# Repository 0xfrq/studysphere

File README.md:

# StudySphere: Smart Study Room (UTS/UAS IoT)

Node IoT berbasis ESP32 untuk ruang belajar pintar. Node membaca suhu, kelembapan, cahaya, kualitas udara dan kehadiran orang, menyalakan lampu belajar secara otomatis, menampilkan status di LCD, dan berkomunikasi dengan aplikasi desktop lewat **MQTT**. Aplikasi desktop (Tauri, Windows dan Linux) ada di `desktop/` dan sekaligus menjadi broker MQTT di laptop, jadi sistemnya berdiri sendiri tanpa internet. LLM lokal dikerjakan terpisah dan memakai kontrak MQTT di bawah.

## Komponen dan wiring

| Komponen | Pin modul | ESP32 | Daya |
|---|---|---|---|
| DHT11 (suhu & kelembapan) | DATA | GPIO4 | 3V3 |
| Modul LDR (LM393) | AO | GPIO34 | 5V |
| MQ-135 (kualitas udara / CO2) | AO | GPIO35 | 5V |
| HC-SR501 PIR (kehadiran) | OUT | GPIO27 | 5V |
| LCD 16x2 I2C (alamat 0x27) | SDA, SCL | GPIO21, GPIO22 | 5V |
| LED lampu belajar + resistor 220 Ω | anoda lewat resistor | GPIO13 | |

Semua GND disambung ke GND ESP32. Rangkaiannya ada di `diagram.json` dan bisa dibuka di WireLab atau Wokwi.

Untuk perangkat asli, pakai PCB di `hardware/` (lihat [PCB dan daftar komponen](#pcb-dan-daftar-komponen)). Bedanya dengan rangkaian simulator:

- Modul LDR diberi daya 3V3, jadi output AO-nya tidak pernah melewati batas ADC ESP32 (sekitar 3,1 V).
- AO MQ-135 bisa sampai 5 V, jadi masuk ke GPIO35 lewat pembagi 10 kΩ/15 kΩ dan maksimal 3,0 V.
- LCD tetap 5 V, tapi SDA dan SCL lewat level shifter BSS138, jadi pin ESP32 hanya melihat 3,3 V.
- Aktifkan `#define REAL_BOARD` di `firmware/config.h`. Firmware lalu membaca tegangan asli dengan `analogReadMilliVolts()` dan menghitung LDR 3,3 V serta pembagi MQ-135. Tanpa itu, firmware memakai skala simulator: ADC ESP32 membaca 0 sampai 5 V sebagai 0 sampai 4095.
- Konstanta kalibrasi LDR dan MQ-135 (`LDR_RL10`, `MQ_RZERO` dan seterusnya) ada di atas `firmware.ino`. `MQ_RZERO` sebaiknya dikalibrasi di udara bersih.
- Modul DHT11 tiga pin sudah punya resistor pull-up. PCB juga punya pull-up 10 kΩ (R1), jadi DHT11 empat pin tanpa modul juga bisa disambung lewat kabel jumper.

## PCB dan daftar komponen

Proyek KiCad 10 ada di `hardware/`; buka `hardware/studysphere.kicad_pro`. ERC dan DRC bersih, dan PCB sama dengan skematik (schematic parity).

| File | Isi |
|---|---|
| `hardware/fab/skematik.pdf` | Skematik untuk laporan atau dicetak |
| `hardware/fab/render-top.png`, `render-bottom.png` | Tampilan 3D PCB |
| `hardware/fab/pcb-top.pdf`, `pcb-bottom.pdf` | Jalur tembaga dan silkscreen tiap sisi |
| `hardware/fab/gerber-jlcpcb.zip` | Gerber dan file drill, siap diunggah ke JLCPCB atau PCBWay |
| `hardware/fab/bom.csv` | Daftar komponen dari KiCad |

PCB 2 layer, 102 × 62 mm, tebal 1,6 mm, dengan lubang M3 di keempat sudut. ESP32-DevKitC V4 ditancap ke dua female header 1x19 (jarak baris 25,4 mm): antena di tepi atas, USB di tepi bawah. Di bawah antena tidak ada tembaga. Kedua sisi PCB diisi GND. Jalur daya 0,6 mm, jalur sinyal 0,3 mm.

**Komponen yang disolder ke PCB**

| Jumlah | Komponen | Ref | Fungsi |
|---|---|---|---|
| 6 | Resistor 10 kΩ 1/4 W | R1, R2, R4, R5, R6, R7 | Pull-up DHT11, pembagi MQ-135 (atas), pull-up I2C |
| 1 | Resistor 15 kΩ 1/4 W | R3 | Pembagi MQ-135 (bawah) |
| 1 | Resistor 220 Ω 1/4 W | R8 | Arus LED, sekitar 6 mA |
| 2 | Kapasitor keramik 100 nF (kode 104) | C2, C3 | Filter ADC LDR dan MQ-135 |
| 1 | Kapasitor elektrolit 100 µF 16 V | C1 | Menahan lonjakan arus heater MQ-135 |
| 2 | MOSFET N-channel BSS138 (SOT-23) | Q1, Q2 | Level shifter I2C 3,3 V ke 5 V |
| 1 | LED kuning 5 mm | D1 | Lampu belajar |
| 4 | Pin header male 1x3 | J1 sampai J4 | DHT11, PIR, LDR, MQ-135 |
| 1 | Pin header male 1x4 | J5 | LCD I2C (urutan GND, VCC, SDA, SCL seperti backpack-nya) |
| 2 | Female header 1x19 | U1 | Soket ESP32-DevKitC V4 |
| 4 | Baut M3 dan spacer | H1 sampai H4 | Kaki PCB |

**Modul dan lainnya:** ESP32-DevKitC V4 (38 pin), modul DHT11, HC-SR501, modul LDR, modul MQ-135, LCD 16x2 dengan backpack I2C PCF8574, 16 kabel jumper female-female, dan kabel micro-USB data.

- R2 dan R3 sebaiknya metal film 1% supaya faktor pembagi MQ-135 tepat. Resistor lain boleh 5%.
- Sebelum memesan, ukur jarak dua baris pin DevKit kamu: harus 25,4 mm dengan urutan pin seperti DevKitC V4 resmi (3V3, EN, VP sampai 5V di satu sisi). Beberapa klon 38 pin punya jarak atau urutan lain.
- Urutan solder: Q1 dan Q2 dulu (SMD paling kecil), lalu resistor, kapasitor, LED, pin header, dan female header terakhir. Kaki + C1 masuk ke pad bertanda +, kaki pendek LED (katoda) ke pad kotak.
- Di JLCPCB, unggah `gerber-jlcpcb.zip`, pilih 2 layer dan tebal 1,6 mm, pengaturan lain biarkan default. Kalau PCB diubah di KiCad, buat ulang Gerber lewat **File > Fabrication Outputs**.
- Arus total sekitar 450 mA (ESP32 dengan WiFi, heater MQ-135 sekitar 150 mA, backlight LCD), jadi pakai port USB dan kabel yang bagus.

## Cara kerja

- Sensor dibaca setiap 2 detik. Telemetry dikirim setiap 5 detik, dan langsung saat kehadiran atau lampu berubah.
- **Kehadiran:** PIR mendeteksi gerakan. Sesi belajar dimulai saat ada gerakan dan berakhir setelah 60 detik tanpa gerakan (`IDLE_MS`).
- **Lampu belajar:** mode `auto` menyalakan lampu saat ada orang dan cahaya di bawah 150 lux (`DARK_LUX`). Mode `on` atau `off` bisa dipilih dari aplikasi desktop.
- **Kualitas udara:** CO2 di atas 1000 ppm (`CO2_STALE`) dianggap `stale`, artinya ruangan perlu dibuka atau diberi ventilasi.
- **LCD:** baris 1 berisi suhu, kelembapan dan cahaya (`25.0C 50%  500lx`). Baris 2 berisi CO2 dan status koneksi (`CO2  400ppm MQTT`; `WIFI` berarti WiFi tersambung tapi broker belum, `----` berarti offline). Pesan dari aplikasi desktop tampil di LCD selama 30 detik, maksimal 32 karakter untuk dua baris.

## MQTT

Broker: aplikasi desktop di laptop, port 1883 (lihat [Aplikasi desktop](#aplikasi-desktop)). Semua topik diawali `studysphere/room-01/` (`TOPIC_ROOT` dan `DEVICE_ID` di `firmware/config.h`).

| Topik | Arah | Isi |
|---|---|---|
| `studysphere/room-01/telemetry` | node ke desktop | Semua data, setiap 5 detik dan saat ada perubahan |
| `studysphere/room-01/request` | desktop ke node | Semantic selector: data apa yang diminta |
| `studysphere/room-01/response` | node ke desktop | Jawaban untuk request |
| `studysphere/room-01/command` | desktop ke node | Mengatur lampu dan LCD |
| `studysphere/room-01/status` | node ke desktop | `online` atau `offline` (retained; `offline` dikirim broker sebagai last will saat node putus) |

**Telemetry**

```json
{"temperature":25,"humidity":50,"lighting":500,"co2":400,"air_quality":"good","occupancy":false,"session_duration":0,"lamp":"off","lamp_mode":"auto"}
```

**Request dan response.** Formatnya sama dengan proyek semanticiot, jadi LLM yang sudah dilatih dengan format itu bisa langsung dipakai:

```json
{"task":"comfort_check","required_information":["temperature","humidity","noise"]}
```

```json
{"task":"comfort_check","data":{"temperature":25,"humidity":50},"unknown":["noise"]}
```

**Command:**

```json
{"lamp":"on"}
{"lamp":"auto"}
{"lcd":"Waktunya istirahat 5 menit"}
```

Setelah command lampu, node langsung mengirim telemetry baru sebagai konfirmasi.

**Nama informasi yang dikenal node:**

| Nama | Satuan / nilai |
|---|---|
| `temperature` | °C |
| `humidity` | % RH |
| `lighting` | lux |
| `co2` | ppm (perkiraan dari MQ-135) |
| `air_quality` | `good` atau `stale` |
| `occupancy` | `true` / `false` |
| `session_duration` | detik sejak sesi belajar dimulai |
| `lamp` | `on` / `off` |
| `lamp_mode` | `auto`, `on` atau `off` |

Nama lain dikembalikan di `unknown`. Request dan command yang sama juga bisa dikirim lewat Serial, satu baris JSON per perintah.

## Konfigurasi

Semua pengaturan jaringan ada di `firmware/config.h`: SSID dan password WiFi, host dan port broker, user dan password MQTT, `TOPIC_ROOT` dan `DEVICE_ID`. `MQTT_HOST` otomatis `127.0.0.1` di simulator lokal WireLab (makro `WIRELAB_SIM`). Untuk board asli, isi dengan IP laptop yang ditampilkan aplikasi desktop.

## Aplikasi desktop

Aplikasi di `desktop/` adalah *island*: pulau hitam kecil yang menggantung di tengah atas layar, dengan maskot burung hantu yang menjaga ruang belajar. Wajah dan kalimat burung hantu mengikuti keadaan ruangan: tidur saat ruangan kosong, senang saat ada yang belajar, pusing saat udara pengap, dan kaget saat node tidak mengirim data.

| Yang dilakukan | Yang terjadi |
|---|---|
| Arahkan mouse ke garis kecil di tengah atas layar | Island muncul satu baris: suhu, kelembapan, CO2 dan lampu |
| Klik island | Island terbuka: semua data, mode lampu (auto, on, off) dan pesan untuk LCD |
| `Esc`, atau mouse keluar | Island menutup lagi (8 detik setelah terbuka, 20 detik setelah satu baris) |
| Udara pengap atau node putus | Island terbuka sendiri |
| Tombol **Quit** di island yang terbuka | Menutup aplikasi |
| Shortcut keyboard, tombol mic, atau ketik di kolom obrolan | Ngobrol dengan burung hantu: tanya keadaan ruangan atau minta ia mengubah sesuatu (lihat di bawah) |
| Udara pengap atau ruangan terlalu panas | Burung hantu langsung bicara memberi tahu, lalu mengingatkan lagi tiap 10 menit selama keadaannya belum membaik |

Saat dibuka, aplikasi menjalankan broker MQTT sendiri di port 1883 pada semua interface laptop, jadi tidak perlu Mosquitto atau internet. Kalau port 1883 sudah dipakai broker lain (misalnya Mosquitto), aplikasi memakai broker itu. Aplikasi mengikuti `DEVICE_ID` apa pun yang mengirim telemetry.

### Ngobrol dengan burung hantu

Tekan shortcut (atau tombol mic) lalu bicara: island terbuka, burung hantu berbunyi "hoo-hoo" dan mendengarkan. Rekaman berhenti sendiri saat kamu diam, atau tekan shortcut/mic lagi untuk langsung mengirim; `Esc` membatalkan, dan menekan lagi saat burung hantu bicara membuatnya diam. Mic hanya terbuka selama ia mendengarkan. Batas suara mengikuti noise ruangan dan bisa disetel lewat `VOICE_RATIO` dan `VOICE_MIN` di `desktop/ui/index.html` (`node desktop/ears.test.js` mengecek kapan rekaman berhenti). Bisa juga mengetik di kolom obrolan.

| Sistem | Shortcut |
|---|---|
| Windows, macOS, Linux X11 | `Ctrl+Alt+Space`, langsung dari aplikasi (kalau sudah dipakai aplikasi lain, hint di island tidak menyebutnya) |
| Linux Wayland (Hyprland, Sway, KDE, GNOME) | Aplikasi tidak bisa memasang shortcut global sendiri di Wayland. Buat shortcut di desktop yang menjalankan `studysphere --talk`; perintah itu diteruskan ke aplikasi yang sedang jalan |

Contoh Hyprland (config Lua), `SUPER + H`:

```lua
hl.bind("SUPER + H", hl.dsp.exec_cmd("studysphere --talk")) -- StudySphere: talk to the owl
```

Saat development (`npm run tauri dev`), ganti `studysphere` dengan path lengkap `desktop/src-tauri/target/debug/studysphere`. Aplikasi hanya jalan satu instance: membukanya lagi tidak membuat island kedua.

Burung hantu juga bicara sendiri kalau ruangan sudah parah: udara pengap (CO2 di atas 1000 ppm, atau MQ-135 stasiun `poor`/alarm) atau suhu 32 °C ke atas (`HOT_C`). Ia memberi tahu apa yang harus dilakukan, dalam Bahasa Indonesia (atau bahasa yang terakhir kamu pakai dengannya), dan mengulang tiap 10 menit (`REMIND_MS`) selama keadaannya belum membaik. Burung hantu menjawab lewat suara dan balon kata, dalam bahasa yang kamu pakai, dan bisa menjalankan perintah ke node: lampu (auto, on, off) dan LCD untuk `firmware/`, atau kipas, ventilasi dan LCD untuk stasiun di `alatnya cu/`. Perintah dari LLM hanya diteruskan kalau nilainya sama dengan yang bisa dikirim tombol.

| Bagian | Sekarang (sementara) | Diatur lewat |
|---|---|---|
| Speech to text | Groq `whisper-large-v3-turbo` | |
| Otak (chat) | Groq `openai/gpt-oss-120b`, endpoint OpenAI-compatible | `STUDYSPHERE_LLM_URL`, `STUDYSPHERE_LLM_MODEL`, `STUDYSPHERE_LLM_KEY` |
| Suara | Groq `canopylabs/orpheus-v1-english` (suara bahasa Inggris, tapi kalimat Indonesia tetap jelas) | |

API key Groq dibaca dari environment shell yang menjalankan aplikasi: `GROQ_API_KEY`, atau `GROQ_API_KEY1` sampai `GROQ_API_KEY9`. Aplikasi mencoba key satu per satu sampai ada yang berhasil, jadi key yang kena rate limit dilewati. Model TTS Orpheus harus di-*accept terms*-nya dulu oleh admin org di [console Groq](https://console.groq.com/playground?model=canopylabs%2Forpheus-v1-english); tanpa itu burung hantu tetap menjawab, hanya tanpa suara. Kalau aplikasi dibuka dari menu desktop (bukan dari terminal), variabel ini harus ada di environment sesi login.

Untuk pindah ke model SFT lokal di Ollama, jalankan aplikasi dengan:

```sh
STUDYSPHERE_LLM_URL=http://localhost:11434/v1 STUDYSPHERE_LLM_MODEL=nama-model-sft npm run tauri dev
```

Model menerima system prompt berisi data ruangan terbaru dan daftar perintah yang boleh dipakai, lalu harus menjawab satu objek JSON: `{"say": "...", "mood": "happy", "command": {"lamp": "on"}}` (`command` boleh `null`). Data latih SFT sebaiknya memakai format yang sama. Di Windows, Ollama perlu `OLLAMA_ORIGINS=*` supaya bisa dipanggil dari aplikasi. Whisper dan suara tetap memakai Groq sampai ada pengganti lokal.

Panduan lengkap untuk membuat dan memasang model lokal sendiri — dataset sintetis, LoRA Gemma 3 270M + Qwen3 1.7B, evaluasi, sampai integrasi dua tahap — ada di [`ai/README.md`](ai/README.md). Untuk training di Colab, gunakan notebook [`studysphere_colab.ipynb`](studysphere_colab.ipynb); checkpoint otomatis disimpan ke Google Drive dan bisa dilanjutkan setelah runtime habis. Kalau GPU Colab sedang tidak tersedia, step ringan di laptop 4 GB ada di [`LOCAL_TRAINING.md`](LOCAL_TRAINING.md).

Screenshot island (tersembunyi, satu baris, terbuka) ada di `desktop/screenshots/`.

Di Linux, island memakai layer-shell supaya tetap di atas layar (KDE, Hyprland, Sway, COSMIC). Pasang `gtk-layer-shell` (Arch) atau `libgtk-layer-shell0` (Debian/Ubuntu). Tanpa itu, atau di GNOME, island menjadi jendela biasa yang selalu di atas, dan posisinya ditentukan oleh desktop.

Syarat untuk build: [Rust](https://rustup.rs), Node.js, dan prasyarat Tauri untuk sistemnya ([daftar lengkap](https://v2.tauri.app/start/prerequisites/)): di Linux `webkit2gtk-4.1`, di Windows Microsoft C++ Build Tools (WebView2 sudah ada di Windows 10 dan 11).

```sh
cd desktop
npm install
npm run tauri dev     # jalankan
npm run tauri build   # installer: .msi dan .exe di Windows, .deb, .rpm dan .AppImage di Linux
```

Installer Windows harus di-build di Windows (Tauri tidak bisa cross-compile dari Linux). Hasilnya ada di `desktop/src-tauri/target/release/bundle/`.

Supaya ESP32 asli bisa tersambung ke laptop:

- ESP32 dan laptop harus di WiFi yang sama. WiFi kampus sering memblokir koneksi antar perangkat; kalau begitu, pakai hotspot HP atau hotspot laptop.
- Windows menanyakan izin firewall saat aplikasi pertama kali dibuka. Izinkan untuk jaringan **Private**, lalu pastikan WiFi-nya diset sebagai Private. Di Linux dengan ufw: `sudo ufw allow 1883/tcp`.
- Broker tidak memakai password, jadi siapa pun di WiFi yang sama bisa membaca dan mengirim command. Untuk presentasi di jaringan bersama, pakai hotspot sendiri.

## Menjalankan

### Di simulator WireLab (lokal, tanpa kuota)

Buka aplikasi desktop, lalu buka folder ini di WireLab dan tekan **Run**. Proyek ini memakai **simulator lokal** WireLab (`"engine": "local"` di `wirelab.json`):

- Firmware di-compile untuk PC dan berjalan di PC, jadi tidak memakai server atau kuota Wokwi.
- WiFi memakai jaringan PC, dan node tersambung ke broker aplikasi desktop di `127.0.0.1:1883`.
- Sensor diatur dengan mengklik part saat simulasi berjalan: slider cahaya (LDR), CO2 (MQ-135), suhu dan kelembapan (DHT11), serta tombol gerakan (PIR). LED dan LCD ikut menampilkan hasilnya.
- Syaratnya: compiler C++ (`g++` atau `clang++`) dan arduino-cli.

Simulator lokal mensimulasikan perilaku, bukan chip-nya: timing sinyal DHT11 dan I2C LCD tidak disimulasikan (library-nya diganti versi tiruan yang memakai nilai dari WireLab). Untuk menguji di mesin Wokwi, ganti simulator di **Settings** (memakai kuota CI: akun Free mendapat 50 menit per 30 hari), atau jalankan perintah di bawah. Mesin Wokwi berjalan di server Wokwi, jadi tidak bisa menjangkau broker di laptop; tes ini hanya memakai Serial.

```sh
arduino-cli compile --fqbn esp32:esp32:esp32 --output-dir firmware/build firmware
wokwi-cli --scenario test.scenario.yaml --timeout 60000 .
```

### Stasiun ESP32 + UNO (`alatnya cu/`) di WireLab

`alatnya cu/` juga proyek WireLab sendiri: buka folder itu di WireLab (**Open…**), lalu tekan **Run**. Rangkaiannya (`alatnya cu/diagram.json`) sama dengan alat fisiknya. ESP32 memakai DHT11, HC-SR04, servo SG90 dan LCD; UNO memakai MQ-135, modul LDR, LCD dan kipas di D13+D12; keduanya tersambung lewat UART D1→GPIO27 dan GPIO26→D0. Kedua sketch dijalankan apa adanya, tanpa diubah.

- `wirelab.json` menentukan sketch untuk tiap board (`"boards"`) dan mengalihkan `MQTT_HOST` di sketch ESP32 (`192.168.1.10`) ke broker aplikasi desktop di laptop ini (`"hosts"`).
- Saat simulasi berjalan, klik part untuk mengatur jarak HC-SR04, cahaya, MQ-135, serta suhu dan kelembapan. Kipas berputar saat menyala, servo ikut bergerak, dan kedua LCD tampil.
- Simulasi memakai `DEVICE_ID` yang sama dengan alat fisik (`station01`). Matikan alat fisiknya dulu supaya perintah dari desktop tidak sampai ke dua-duanya.
- MQ-135 tetap butuh pemanasan 2 menit (`MQ_WARMUP_MS` di sketch UNO), sama seperti di alat fisik.

### Di ESP32 asli

1. Pasang library (sekali saja):
   ```sh
   arduino-cli lib install "DHT sensor library" "Adafruit Unified Sensor" "LiquidCrystal I2C" PubSubClient ArduinoJson
   ```
2. Isi WiFi kamu dan `MQTT_HOST` (IP laptop, ditampilkan aplikasi desktop) di `firmware/config.h`, dan aktifkan `#define REAL_BOARD` di file yang sama (rangkaian PCB di `hardware/`).
3. Compile, upload, lalu lihat serial monitor (ganti `/dev/ttyUSB0` sesuai port ESP32):
   ```sh
   arduino-cli compile --fqbn esp32:esp32:esp32 firmware
   arduino-cli upload -p /dev/ttyUSB0 --fqbn esp32:esp32:esp32 firmware
   arduino-cli monitor -p /dev/ttyUSB0 -c baudrate=115200
   ```
4. Buka aplikasi desktop. Serial monitor menampilkan `MQTT connected` setelah node tersambung.

## Mengetes MQTT tanpa aplikasi desktop

Selama aplikasi desktop terbuka, broker-nya bisa dipakai alat lain. Pakai [MQTT Explorer](https://mqtt-explorer.com/) (GUI), atau `mosquitto_sub` / `mosquitto_pub` dari paket mosquitto:

```sh
# lihat semua pesan dari node
mosquitto_sub -h localhost -t 'studysphere/room-01/#' -v

# minta data seperti yang akan dilakukan LLM
mosquitto_pub -h localhost -t studysphere/room-01/request \
  -m '{"task":"comfort_check","required_information":["temperature","humidity","co2"]}'

# atur lampu dan LCD
mosquitto_pub -h localhost -t studysphere/room-01/command -m '{"lamp":"on"}'
mosquitto_pub -h localhost -t studysphere/room-01/command -m '{"lcd":"Waktunya istirahat"}'
```

## Struktur folder

```text
firmware/firmware.ino   program ESP32
firmware/config.h       WiFi, broker MQTT, topik
desktop/                aplikasi desktop dan broker MQTT (Tauri)
desktop/screenshots/    screenshot UI desktop
alatnya cu/             stasiun ESP32 + UNO, dengan proyek WireLab-nya
hardware/               skematik, PCB dan library KiCad 10
hardware/fab/           PDF skematik, BOM, Gerber, render PCB
diagram.json            rangkaian (WireLab / Wokwi)
wokwi.toml              lokasi firmware dan custom chip untuk simulator
chips/                  DHT11, MQ-135 dan HC-SR501 untuk simulator
test.scenario.yaml      tes otomatis lewat Serial di simulator
libraries.txt           daftar library Arduino
```

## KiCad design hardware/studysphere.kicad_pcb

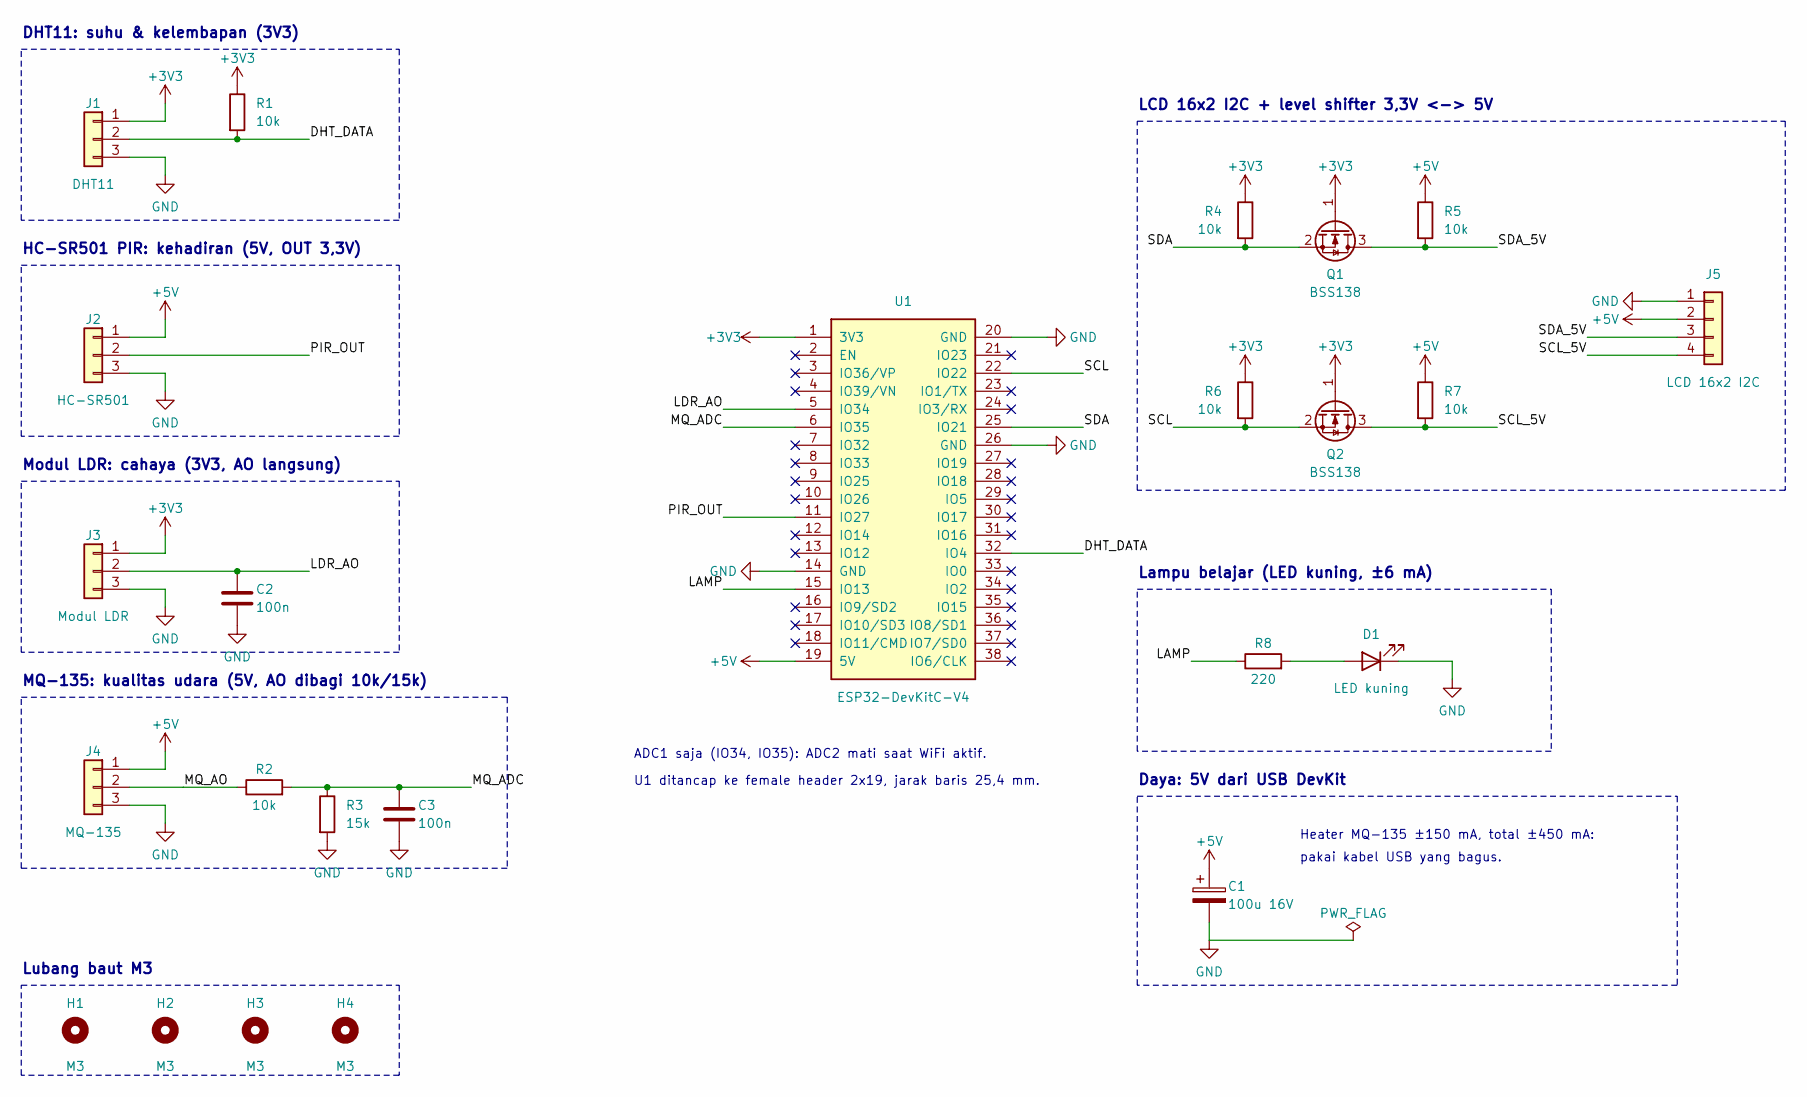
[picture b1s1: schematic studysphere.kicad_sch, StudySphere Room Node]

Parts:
C1: 100u 16V; CP_Radial_D6.3mm_P2.50mm
C2, C3: 100n; C_Disc_D5.0mm_W2.5mm_P5.00mm
D1: LED kuning; LED_D5.0mm
H1, H2, H3, H4: M3; MountingHole_3.2mm_M3
J1: DHT11; PinHeader_1x03_P2.54mm_Vertical
J2: HC-SR501; PinHeader_1x03_P2.54mm_Vertical
J3: Modul LDR; PinHeader_1x03_P2.54mm_Vertical
J4: MQ-135; PinHeader_1x03_P2.54mm_Vertical
J5: LCD 16x2 I2C; PinHeader_1x04_P2.54mm_Vertical
Q1, Q2: BSS138; SOT-23
R1, R2, R4, R5, R6, R7: 10k; R_Axial_DIN0207_L6.3mm_D2.5mm_P10.16mm_Horizontal
R3: 15k; R_Axial_DIN0207_L6.3mm_D2.5mm_P10.16mm_Horizontal
R8: 220; R_Axial_DIN0207_L6.3mm_D2.5mm_P10.16mm_Horizontal
U1: ESP32-DevKitC-V4; ESP32-DevKitC-V4_Socket

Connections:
+3V3: J1.1, J3.1, Q1.1 (G), Q2.1 (G), R1.1, R4.1, R6.1, U1.1 (3V3)
+5V: C1.1, J2.1, J4.1, J5.2, R5.1, R7.1, U1.19 (5V)
/DHT_DATA: J1.2, R1.2, U1.32 (IO4)
/LAMP: R8.1, U1.15 (IO13)
/LDR_AO: C2.1, J3.2, U1.5 (IO34)
/MQ_ADC: C3.1, R2.2, R3.1, U1.6 (IO35)
/MQ_AO: J4.2, R2.1
/PIR_OUT: J2.2, U1.11 (IO27)
/SCL: Q2.2 (S), R6.2, U1.22 (IO22)
/SCL_5V: J5.4, Q2.3 (D), R7.2
/SDA: Q1.2 (S), R4.2, U1.25 (IO21)
/SDA_5V: J5.3, Q1.3 (D), R5.2
GND: C1.2, C2.2, C3.2, D1.1 (K), J1.3, J2.3, J3.3, J4.3, J5.1, R3.2, U1.14 (GND), U1.20 (GND), U1.26 (GND)
unnamed: D1.2 (A), R8.2

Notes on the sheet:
Heater MQ-135 ±150 mA, total ±450 mA:
HC-SR501 PIR: kehadiran (5V, OUT 3,3V)
Daya: 5V dari USB DevKit
LCD 16x2 I2C + level shifter 3,3V <-> 5V
pakai kabel USB yang bagus.
ADC1 saja (IO34, IO35): ADC2 mati saat WiFi aktif.
MQ-135: kualitas udara (5V, AO dibagi 10k/15k)
Lubang baut M3
Modul LDR: cahaya (3V3, AO langsung)
Lampu belajar (LED kuning, ±6 mA)
U1 ditancap ke female header 2x19, jarak baris 25,4 mm.
DHT11: suhu & kelembapan (3V3)

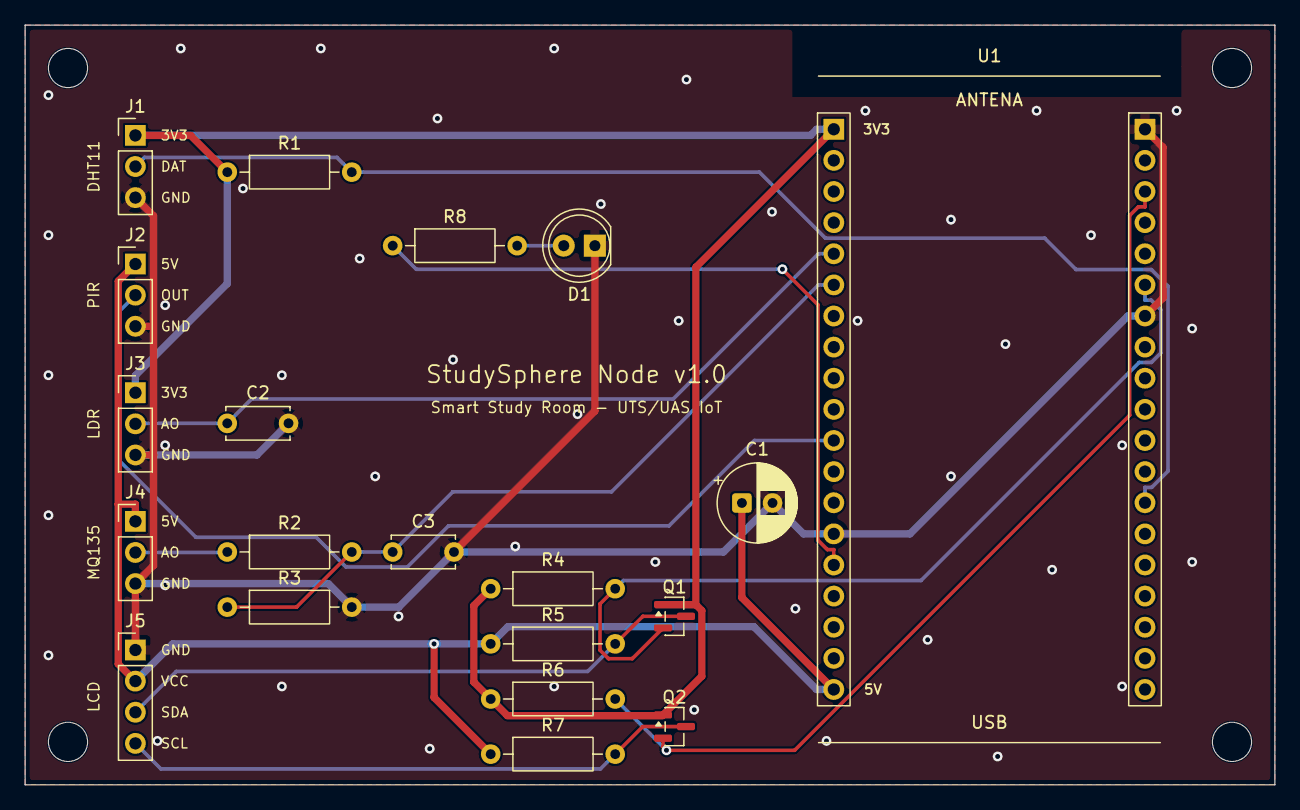
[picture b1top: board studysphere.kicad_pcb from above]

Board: 2 copper layers, 102.0 x 62.0 mm, 24 parts (0 on the bottom side), 14 nets.

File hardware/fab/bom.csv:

"Ref","Value","Footprint","Qty"
"C1","100u 16V","Capacitor_THT:CP_Radial_D6.3mm_P2.50mm","1"
"C2,C3","100n","Capacitor_THT:C_Disc_D5.0mm_W2.5mm_P5.00mm","2"
"D1","LED kuning","LED_THT:LED_D5.0mm","1"
"J1","DHT11","Connector_PinHeader_2.54mm:PinHeader_1x03_P2.54mm_Vertical","1"
"J2","HC-SR501","Connector_PinHeader_2.54mm:PinHeader_1x03_P2.54mm_Vertical","1"
"J3","Modul LDR","Connector_PinHeader_2.54mm:PinHeader_1x03_P2.54mm_Vertical","1"
"J4","MQ-135","Connector_PinHeader_2.54mm:PinHeader_1x03_P2.54mm_Vertical","1"
"J5","LCD 16x2 I2C","Connector_PinHeader_2.54mm:PinHeader_1x04_P2.54mm_Vertical","1"
"Q1,Q2","BSS138","Package_TO_SOT_SMD:SOT-23","2"
"R1,R2,R4,R5,R6,R7","10k","Resistor_THT:R_Axial_DIN0207_L6.3mm_D2.5mm_P10.16mm_Horizontal","6"
"R3","15k","Resistor_THT:R_Axial_DIN0207_L6.3mm_D2.5mm_P10.16mm_Horizontal","1"
"R8","220","Resistor_THT:R_Axial_DIN0207_L6.3mm_D2.5mm_P10.16mm_Horizontal","1"
"U1","ESP32-DevKitC-V4","studysphere:ESP32-DevKitC-V4_Socket","1"
